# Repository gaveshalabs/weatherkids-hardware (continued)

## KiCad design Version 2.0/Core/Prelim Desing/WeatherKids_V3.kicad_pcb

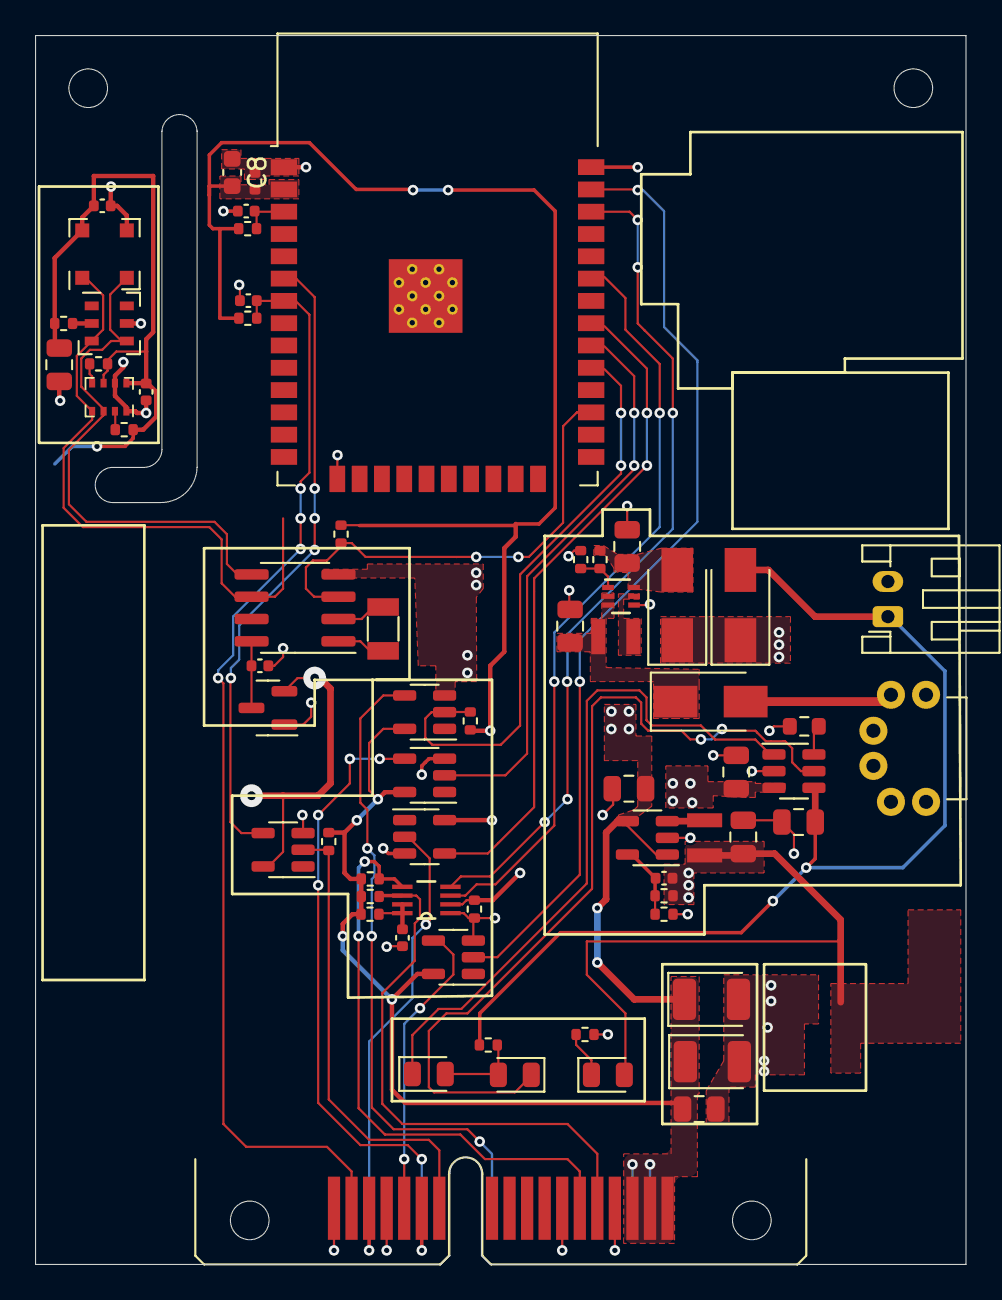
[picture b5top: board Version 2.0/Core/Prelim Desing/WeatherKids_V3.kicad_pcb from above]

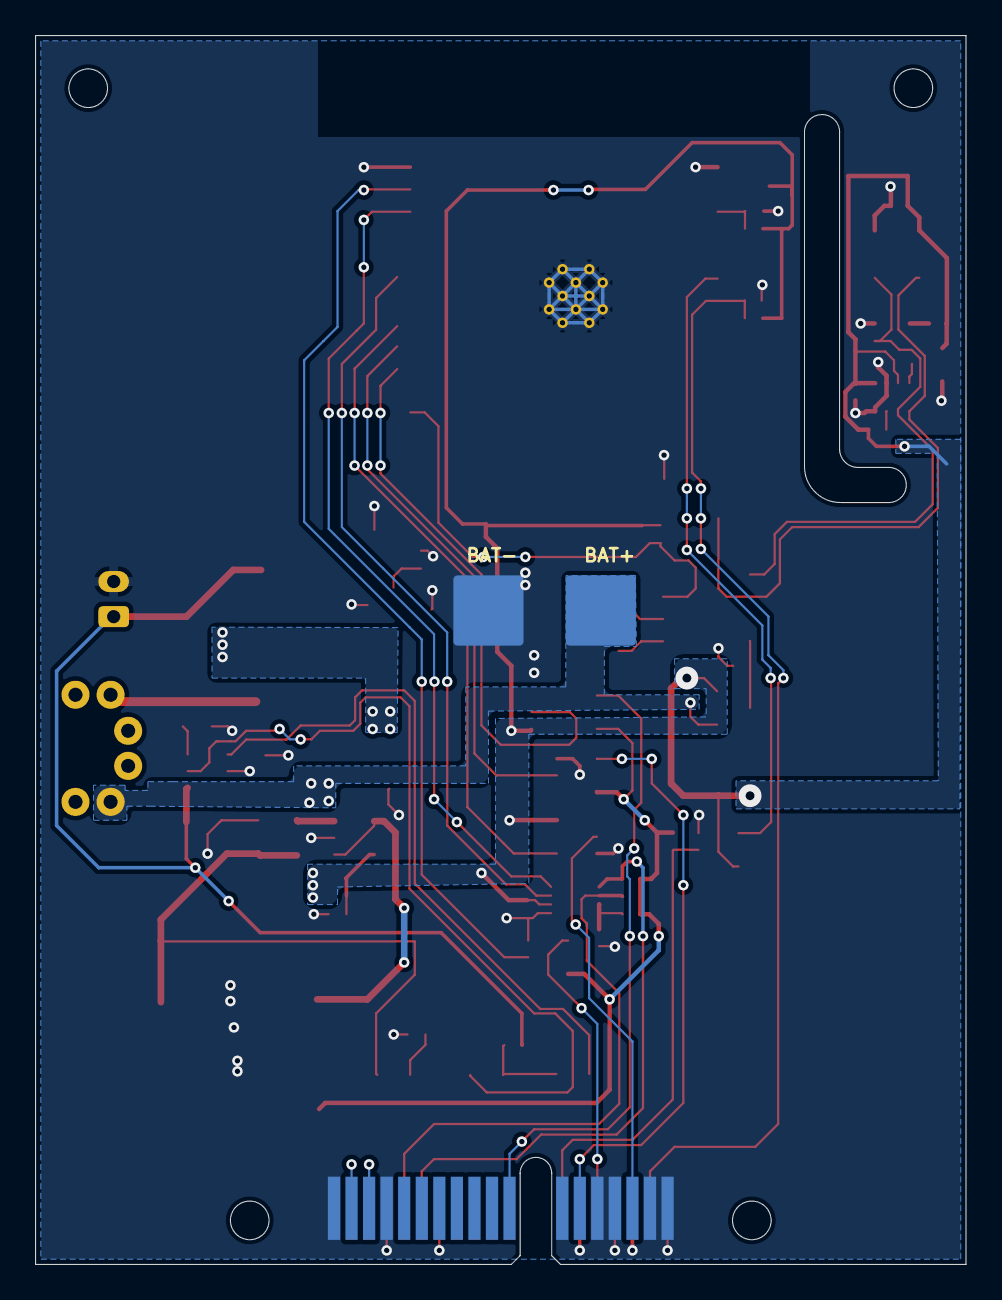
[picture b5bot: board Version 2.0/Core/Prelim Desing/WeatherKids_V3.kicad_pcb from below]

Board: 2 copper layers, 53.0 x 70.0 mm, 69 parts (2 on the bottom side), 43 nets.

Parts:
C2, C4, C5, C6, C9, C12, C14, C21: 10uF; C_0805_2012Metric
C7: 0.1uF; C_0402_1005Metric
C8: 22uF; C_0603_1608Metric
C10: 1nF; C_0402_1005Metric
C11: 12pF; C_0402_1005Metric
C13, C15, C16, C17, C18: 100nF; C_0402_1005Metric
C19, C20: 100uF; CP_EIA-3528-12_Kemet-T
D1, D2, D6: LED; LED_0805_2012Metric
D3, D4, D5: SS54; D_SMA
D7: BAV70; SOT-23
H1, H2: MountingHole; MountingHole_2.2mm_M2
J4: Conn_01x02; JST_PH_S2B-PH-K_1x02_P2.00mm_Horizontal
J5, J8: BAT; SolderWire-2.5sqmm_1x01_D2.4mm_OD4.4mm
J10: 3126-10200D; 3126-XXXX
L1: 1uH; WPN252010U
L2: 2.2uH; WPN252010U
R1: 2k; R_0603_1608Metric
R2, R6, R12: 330R; R_0402_1005Metric
R3: 510k; R_0402_1005Metric
R4: 68k; R_0402_1005Metric
R5, R13, R14, R15, R17, R19, R20, R21, R22: 10k; R_0402_1005Metric
R7: 100k; R_0402_1005Metric
R8: 22k; R_0402_1005Metric
R16: 450k; R_0402_1005Metric
R18: 200k; R_0402_1005Metric
SW1: SW_SPST; XKB5858-X-E
U1: TP4057; SOT-23-6
U2: TPS61023DRL; DRL0006A
U3: ESP32-WROOM-32D; ESP32-WROOM-32
U4: RT8059GJ5; TSOT-23-5
U5: AGS10
U6: AHT20
U7: PCF8563T; SOIC-8_3.9x4.9mm_P1.27mm
U8: BMP280; Bosch_LGA-8_2x2.5mm_P0.65mm_ClockwisePinNumbering
U9: PCA9306DCUR
U10, U11, U12, U13, U14: SN74LV1T34DVBR; SOT-23-5
Y1: 32.768kHz; Crystal_SMD_3215-2Pin_3.2x1.5mm

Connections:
+3V3: C7.2, C8.2, C11.1, C12.1, C13.1, C14.1, C16.1, D6.2 (A), D7.2 (A), L2.2, R5.1, R7.1, R12.1, R13.1, R14.1, R15.1, R16.2, R17.2, R20.2, U3.2 (VDD), U5.4 (VDD), U8.6 (VDDIO), U8.8 (VDD), U9.2 (VREF1), U12.5 (VCC), U13.5 (VCC)
+5V: C9.1, C19.1, C20.1, C21.1, D4.1 (K), D5.1 (K), J10.A2, J10.A3, J10.B1, J10.B2, J10.B3, R18.2, R19.2, R21.2, R22.2, U4.1 (EN), U4.4 (VIN), U10.5 (VCC), U11.5 (VCC), U14.5 (VCC)
+BATT: C5.1, D7.1 (A), J5.1, SW1.4 (A), U1.3 (BAT)
/BAT: C4.1, D3.1 (K), L1.1, U2.2 (EN), U2.3 (VIN)
/Bus/GBUS_5V_MISO: J10.A16, U12.2 (A)
/Bus/GBUS_5V_MOSI: J10.B14, U11.4 (Y)
/Bus/GBUS_5V_SCL: J10.B5, R19.1, U9.6 (SCL2)
/Bus/GBUS_5V_SCLK: J10.A13, U10.4 (Y)
/Bus/GBUS_5V_SDA: J10.B6, R21.1, U9.5 (SDA2)
/Bus/~GBUS_5V_INT: J10.B12, R22.1, U13.2 (A)
/Bus/~GBUS_5V_RESET: J10.A11, U14.4 (Y)
/GBUS.CLK: U3.30 (IO18), U10.2 (A)
/GBUS.DETECT: C18.1, J10.B17, R20.1, U3.7 (IO35)
/GBUS.MISO: U3.31 (IO19), U12.4 (Y)
/GBUS.MOSI: U3.37 (IO23), U11.2 (A)
/GBUS.SCL: U3.33 (IO21), U9.3 (SCL1)
/GBUS.SDA: U3.36 (IO22), U9.4 (SDA1)
/GBUS.~INT: U3.6 (IO34), U13.4 (Y)
/GBUS.~RESET: R17.1, U3.29 (IO5), U14.2 (A)
/I2C_SCL: U3.10 (IO25), U5.1 (SCL), U6.3 (SCL), U7.6 (SCL), U8.4 (SCK)
/I2C_SDA: U3.11 (IO26), U5.2 (SDA), U6.4 (SDA), U7.5 (SDA), U8.3 (SDI)
/~ESP23_EN: C10.1, R5.2, U3.3 (EN)
/~RTC_INT: R13.2, U3.27 (IO16), U7.3 (~INT)
GND: C2.1, C4.2, C5.2, C6.2, C7.1, C8.1, C9.2, C10.2, C12.2, C13.2, C14.2, C15.2, C16.2, C17.2, C18.2, C19.2, C20.2, C21.2, J4.2, J8.1, J10.A1, J10.A4, J10.A12, J10.A14, J10.A15, J10.A17, J10.A18, J10.B4, J10.B7, J10.B13, J10.B15, J10.B16, J10.B18, R1.2, R4.2, R6.1, R8.2, R16.1, U1.2 (GND), U2.4 (GND), U3.1 (GND), U3.15 (GND), U3.38 (GND), U3.39 (GND), U4.2 (GND), U5.3 (GND), U6.5 (GND), U7.4 (VSS), U8.1 (GND), U8.7 (GND), U9.1 (GND), U10.3 (GND), U11.3 (GND), U12.3 (GND), U13.3 (GND), U14.3 (GND)
unnamed: C6.1, D4.2 (A), R3.1, U2.6 (VOUT)
unnamed: C11.2, R7.2, R8.1, U4.5 (FB)
unnamed: C15.1, D7.3 (K), U7.8 (VDD)
unnamed: C17.1, R18.1, U9.7 (VREF2), U9.8 (EN)
unnamed: D1.1 (K), U1.5 (~STDBY)
unnamed: D1.2 (A), D2.2 (A), R2.1
unnamed: D2.1 (K), U1.1 (~CHRG)
unnamed: D3.2 (A), SW1.2 (B)
unnamed: D6.1 (K), R6.2
unnamed: L1.2, U2.5 (SW)
unnamed: L2.1, U4.3 (LX)
unnamed: R1.1, U1.6 (PROG)
unnamed: R3.2, R4.1, U2.1 (FB)
unnamed: R12.2, U6.2 (VDD)
unnamed: R14.2, U8.5 (SDO)
unnamed: R15.2, U8.2 (CSB)
unnamed: U7.1 (OSCI), Y1.2
unnamed: U7.2 (OSCO), Y1.1
VBUS: C2.2, D5.2 (A), J4.1, R2.2, U1.4 (VCC)

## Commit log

2024-11-12 uploading schematics
